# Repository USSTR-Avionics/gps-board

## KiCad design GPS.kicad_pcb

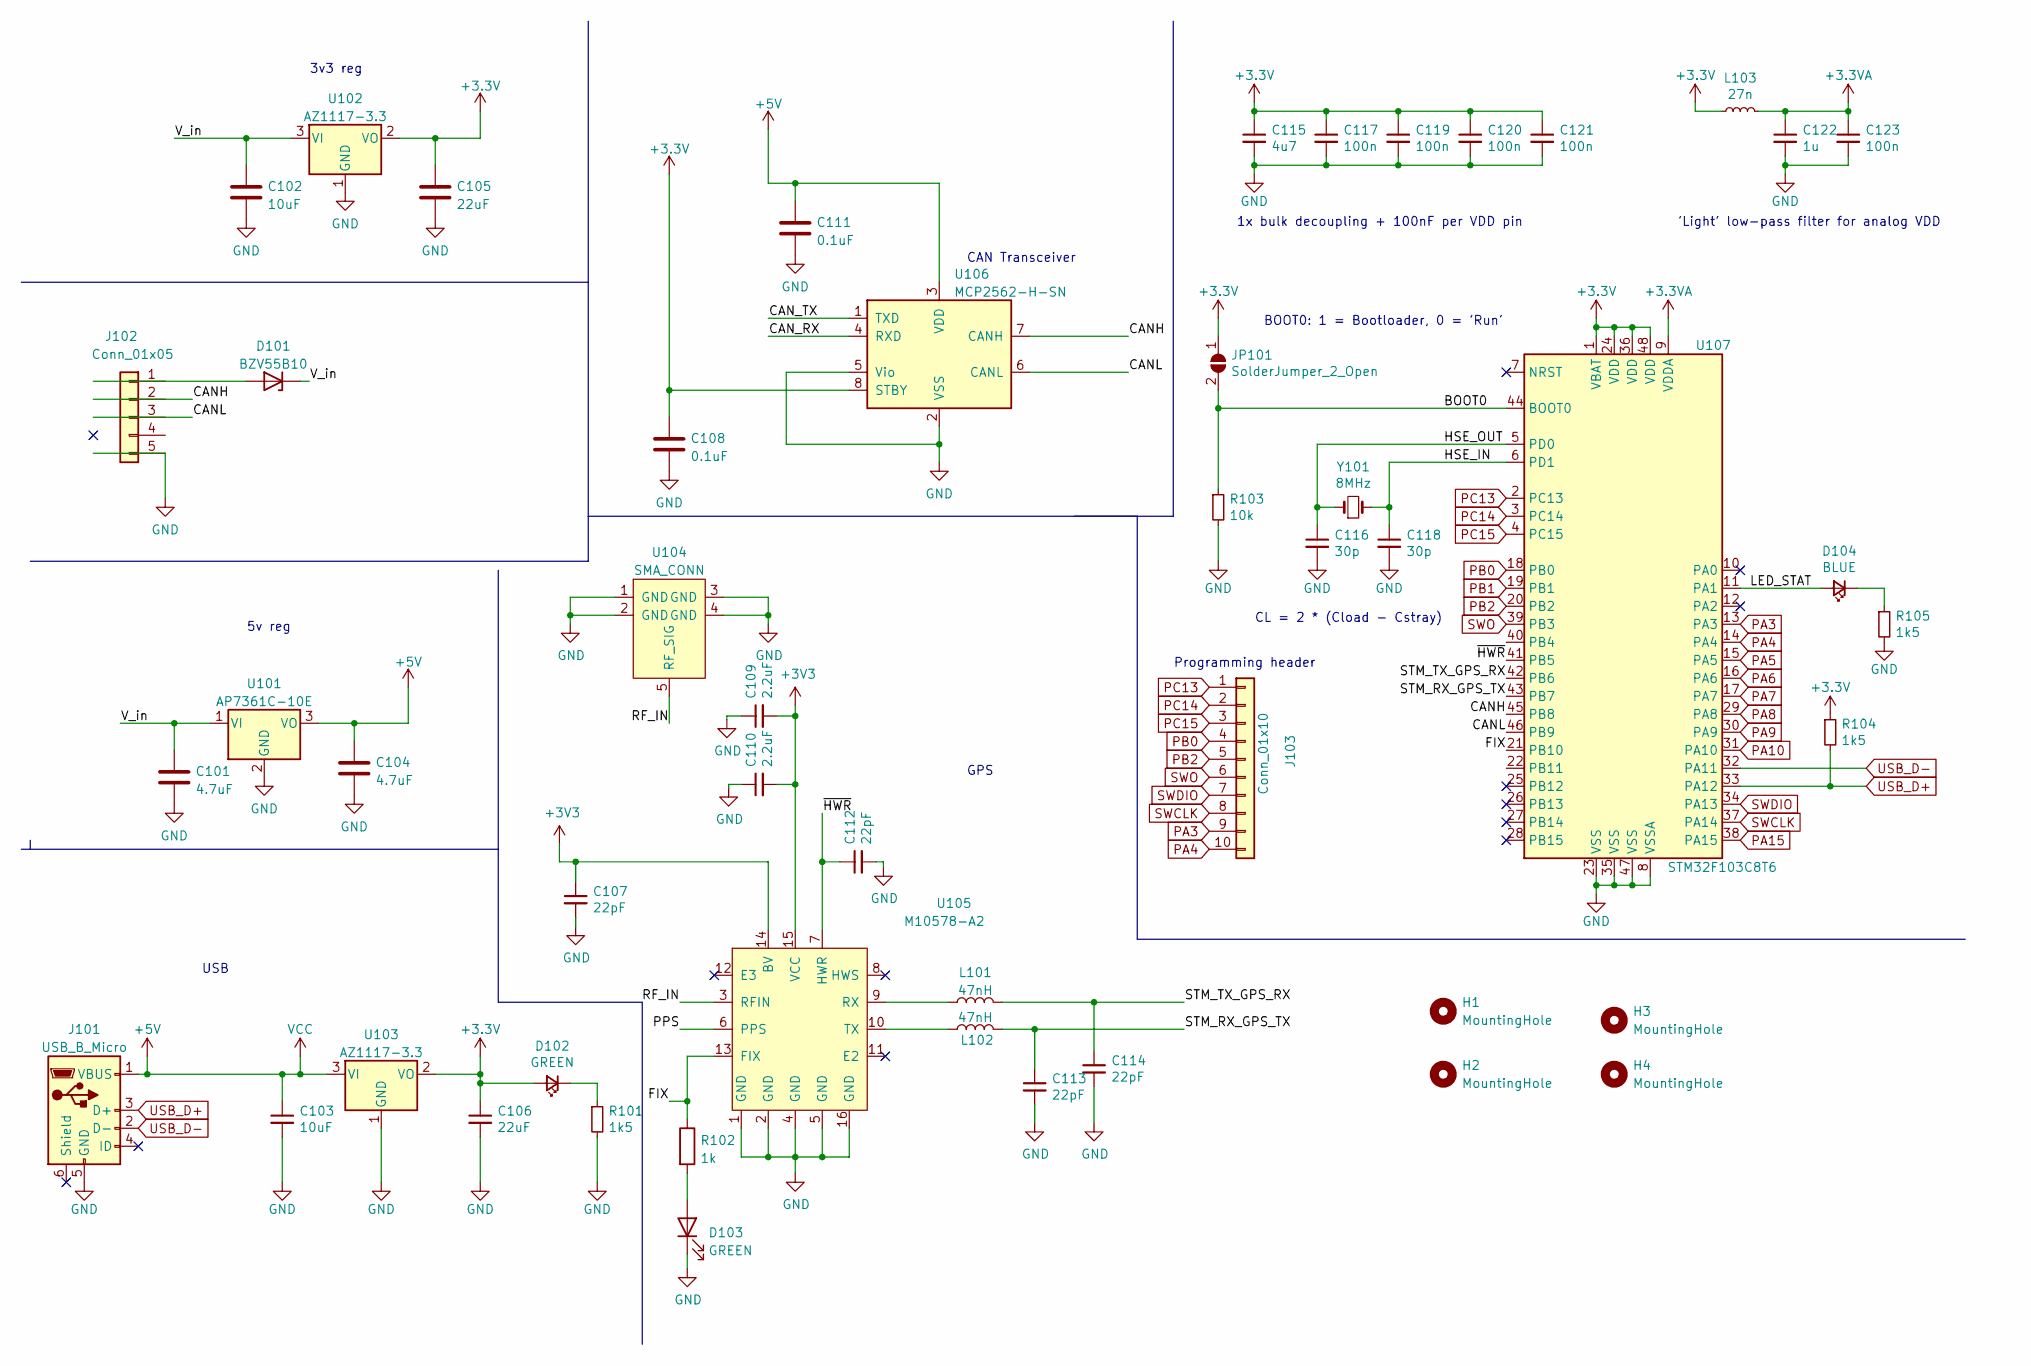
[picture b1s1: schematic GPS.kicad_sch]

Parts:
C101, C104: 4.7uF; C_0805_2012Metric
C102: 10uF; C_0805_2012Metric
C103: 10uF; C_0603_1608Metric; LCSC Part # C15849
C105: 22uF; C_0805_2012Metric
C106: 22uF; C_0805_2012Metric; LCSC Part # C15849
C107, C112, C113, C114: 22pF; C_0805_2012Metric; LCSC Part # C15849
C108, C111: 0.1uF; C_0805_2012Metric
C109, C110: 2.2uF; C_0805_2012Metric; LCSC Part # C15849
C115: 4u7; C_0805_2012Metric; LCSC Part # C19666
C116, C118: 30p; C_0805_2012Metric; LCSC Part # C1570
C117, C119, C120, C121, C123: 100n; C_0805_2012Metric; LCSC Part # C1525
C122: 1u; C_0805_2012Metric; LCSC Part # C52923
D101: BZV55B10; D_MiniMELF
D102: GREEN; LED_0805_2012Metric_Pad1.15x1.40mm_HandSolder; LCSC Part # C72043
D103: GREEN; LED_0805_2012Metric_Pad1.15x1.40mm_HandSolder
D104: BLUE; LED_0603_1608Metric; LCSC Part # C72041
H1, H2, H3, H4: MountingHole; MountingHole_3.2mm_M3
J101: USB_B_Micro; USB_Micro-B_Wuerth_629105150521
J102: Conn_01x05; PinHeader_1x05_P1.27mm_Horizontal
J103: Conn_01x10; PinHeader_1x10_P1.27mm_Horizontal
JP101: SolderJumper_2_Open; SolderJumper-2_P1.3mm_Open_Pad1.0x1.5mm
L101, L102: 47nH; L_0805_2012Metric_Pad1.15x1.40mm_HandSolder
L103: 27n; L_0402_1005Metric; LCSC Part # C18830
R101, R105: 1k5; R_0805_2012Metric; LCSC Part # C22843
R102: 1k; R_0805_2012Metric_Pad1.20x1.40mm_HandSolder
R103: 10k; R_0805_2012Metric; LCSC Part # C25744
R104: 1k5; R_0805_2012Metric; LCSC Part # C25867
U101: AP7361C-10E; SOT-223-3_TabPin2
U102, U103: AZ1117-3.3; SOT-223
U104: SMA_CONN; connector_SMA_3-1478978-1
U105: M10578-A2
U106: MCP2562-H-SN; SOIC-8_3.9x4.9mm_P1.27mm
U107: STM32F103C8T6; LQFP-48_7x7mm_P0.5mm; LCSC Part # C8734
Y101: 8MHz; Crystal_SMD_5032-2Pin_5.0x3.2mm; LCSC Part # C115962

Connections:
+3.3V: C105.1, C106.1, C108.1, C115.1, C117.1, C119.1, C120.1, C121.1, D102.2 (A), JP101.1 (A), L103.1, R104.1, U102.2 (VO), U103.2 (VO), U106.8 (STBY), U107.1 (VBAT), U107.24 (VDD), U107.36 (VDD), U107.48 (VDD)
+3.3VA: C122.1, C123.1, L103.2, U107.9 (VDDA)
+3V3: C107.1, C109.2, C110.2, U105.14 (BV), U105.15 (VCC)
+5V: C103.1, C104.1, C111.1, J101.1 (VBUS), U101.3 (VO), U103.3 (VI), U106.3 (VDD)
/BOOT0: JP101.2 (B), R103.1, U107.44 (BOOT0)
/CANH: U106.7 (CANH), U107.45 (PB8)
/CANL: U106.6 (CANL), U107.46 (PB9)
/CAN_RX: U106.4 (RXD)
/CAN_TX: U106.1 (TXD)
/FIX: R102.1, U105.13 (FIX), U107.21 (PB10)
/HSE_IN: C118.1, U107.6 (PD1), Y101.2
/HSE_OUT: C116.1, U107.5 (PD0), Y101.1
/LED_STAT: D104.2 (A), U107.11 (PA1)
/PPS: U105.6 (PPS)
/RF_IN: U104.5 (RF_SIG), U105.3 (RFIN)
/STM_RX_GPS_TX: C113.1, L102.2, U107.43 (PB7)
/STM_TX_GPS_RX: C114.1, L101.2, U107.42 (PB6)
/V_in: C101.1, C102.1, D101.1 (K), U101.1 (VI), U102.3 (VI)
/~HWR: C112.1, U105.7 (HWR), U107.41 (PB5)
GND: C101.2, C102.2, C103.2, C104.2, C105.2, C106.2, C107.2, C108.2, C109.1, C110.1, C111.2, C112.2, C113.2, C114.2, C115.2, C116.2, C117.2, C118.2, C119.2, C120.2, C121.2, C122.2, C123.2, D103.1 (K), J101.5 (GND), J102.5, R101.2, R103.2, R105.2, U101.2 (GND), U102.1 (GND), U103.1 (GND), U104.1 (GND), U104.2 (GND), U104.3 (GND), U104.4 (GND), U105.1 (GND), U105.2 (GND), U105.4 (GND), U105.5 (GND), U105.16 (GND), U106.2 (VSS), U106.5 (Vio), U107.8 (VSSA), U107.23 (VSS), U107.35 (VSS), U107.47 (VSS)
unnamed: D102.1 (K), R101.1
unnamed: D103.2 (A), R102.2
unnamed: D104.1 (K), R105.1
unnamed: L101.1, U105.9 (RX)
unnamed: L102.1, U105.10 (TX)
PA3: J103.9, U107.13 (PA3)
PA4: J103.10, U107.14 (PA4)
PA5: U107.15 (PA5)
PA6: U107.16 (PA6)
PA7: U107.17 (PA7)
PA8: U107.29 (PA8)
PA9: U107.30 (PA9)
PA10: U107.31 (PA10)
PA15: U107.38 (PA15)
PB0: J103.4, U107.18 (PB0)
PB1: U107.19 (PB1)
PB2: J103.5, U107.20 (PB2)
PC13: J103.1, U107.2 (PC13)
PC14: J103.2, U107.3 (PC14)
PC15: J103.3, U107.4 (PC15)
SWCLK: J103.8, U107.37 (PA14)
SWDIO: J103.7, U107.34 (PA13)
SWO: J103.6, U107.39 (PB3)
USB_D+: J101.3 (D+), R104.2, U107.33 (PA12)
USB_D-: J101.2 (D-), U107.32 (PA11)

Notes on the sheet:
USB
BOOT0: 1 = Bootloader, 0 = 'Run'
CAN Transceiver
5v reg
Programming header
1x bulk decoupling + 100nF per VDD pin
'Light' low-pass filter for analog VDD
GPS
CL = 2 * (Cload - Cstray)
3v3 reg

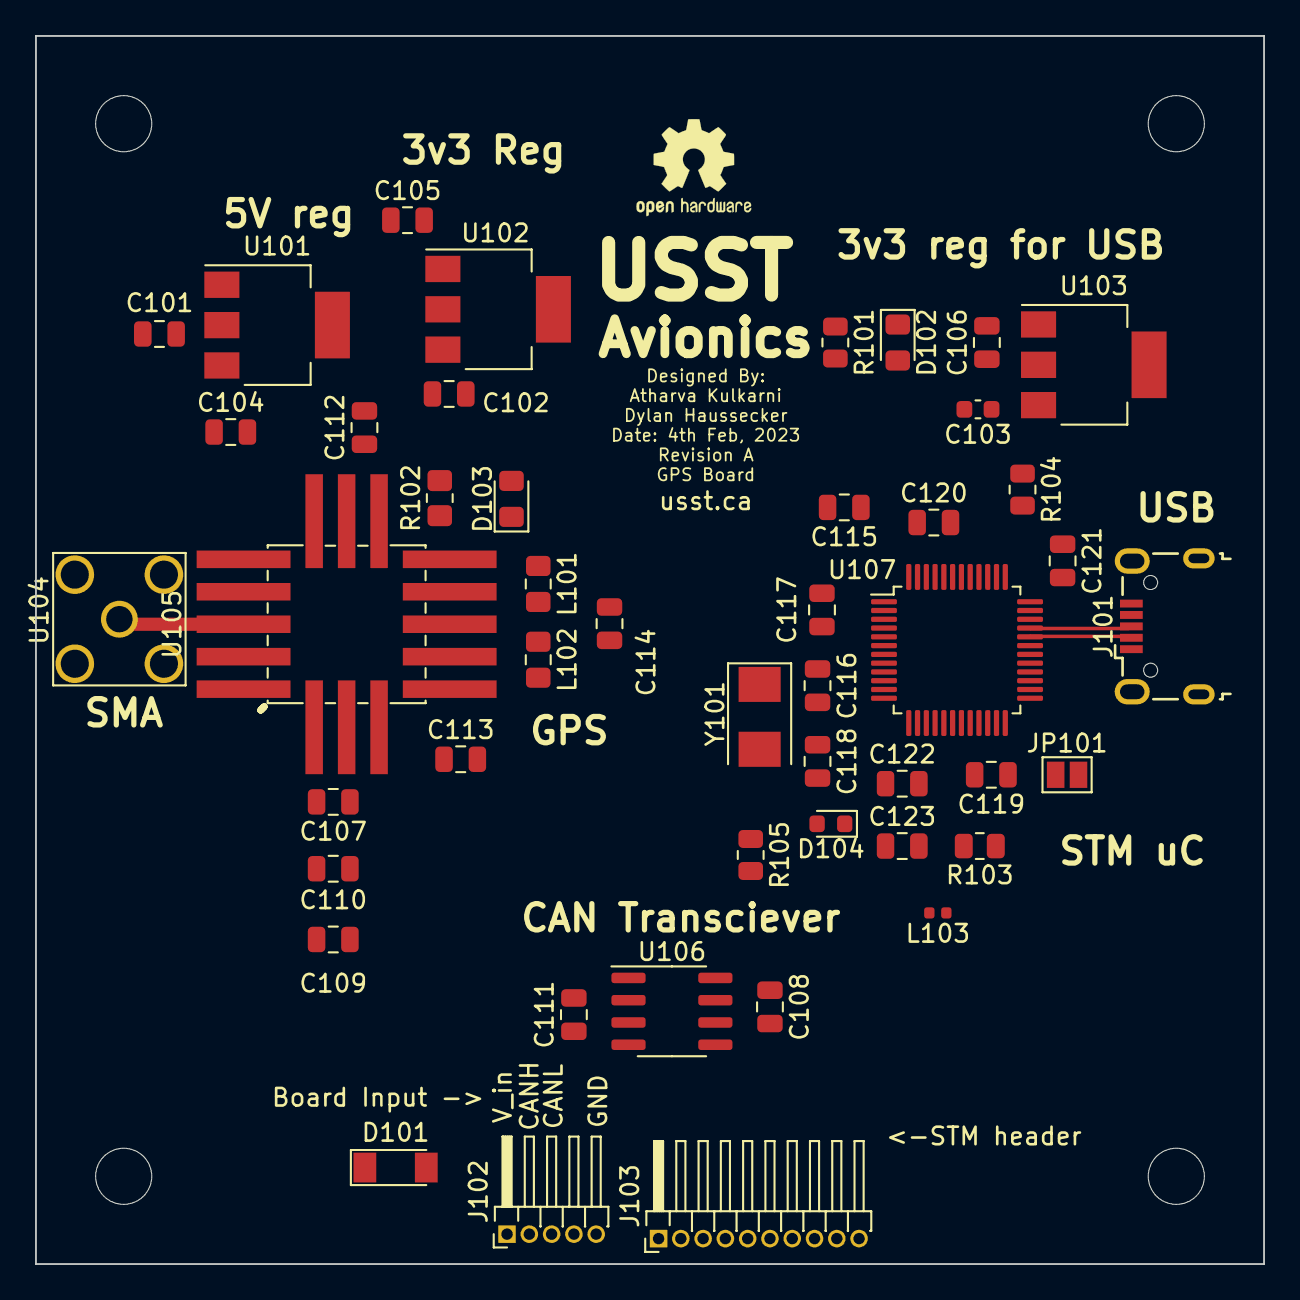
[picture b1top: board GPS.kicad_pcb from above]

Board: 2 copper layers, 70.0 x 70.0 mm, 51 parts (0 on the bottom side), 34 nets.

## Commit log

2023-02-08 Add files via upload
    Updated PCB layout with proper RF traces and differential pairs. PCB dimensions are now 70 mm by 70 mm
2023-02-12 made changes for CANH/L and added STM programming header
2023-02-12 gerbers
2023-02-12 push for production rev A
2023-02-19 added pdf of schematic
